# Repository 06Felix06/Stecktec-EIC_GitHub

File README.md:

# Stecktec EIC – Easy Irrigation Control

**Ein modulares, solarbetriebenes Bewässerungssystem mit eigenen Platinen, LoRa-Funk, Mobilfunk-Anbindung und Smartphone-App.**

Maturaprojekt (Abschlussprojekt) im Schuljahr 2024/25 an der Technologischen Fachoberschule Meran „Oskar von Miller“, Fachrichtung Elektrotechnik – von Felix Steck.

<p align="center">
  
  &nbsp;
  
</p>

<p align="center"><em>Hauptplatine (links) und Sensorplatine (rechts) – beide selbst in KiCad entworfen</em></p>

**Die komplette Projektdokumentation (64 Seiten) liegt hier: [docs/Projektdokumentation_StecktecEIC.pdf](docs/Projektdokumentation_StecktecEIC.pdf)**

---

## Inhalt

- [Was ist Stecktec EIC?](#was-ist-stecktec-eic)
- [Idee und Motivation](#idee-und-motivation)
- [Wie das System funktioniert](#wie-das-system-funktioniert)
- [Hardware](#hardware)
- [Software](#software)
- [Was nicht nach Plan lief](#was-nicht-nach-plan-lief)
- [Projekt in Zahlen](#projekt-in-zahlen)
- [Aufbau des Repositorys](#aufbau-des-repositorys)
- [Fazit](#fazit)
- [Lizenz](#lizenz)

---

## Was ist Stecktec EIC?

Stecktec EIC ist ein modulares intelligentes Bewässerungssystem, das speziell für den Einsatz im Obst- und Beerenanbau, aber auch für private Gärten konzipiert wurde. Es besteht aus mehreren modularen Teilen und kann verschiedene Werte wie die Bodenfeuchtigkeit, Temperatur und Luftfeuchtigkeit messen und Bewässerungsventile schalten. Alles wird über eine benutzerfreundliche Smartphone-App gesteuert und überwacht. Das ermöglicht dem Bauern eine optimale Übersicht und Kontrolle über seine Felder.

**EIC** steht für **Easy Irrigation Control** – eine einfache und effiziente Steuerung der Bewässerung, mit dem Ziel, den Wasserverbrauch zu verringern.

Kurz gesagt kann das System:

- **Bodenfeuchte messen** – mit einem Watermark-Saugspannungssensor (Irrometer 200SS), der misst, wie viel Wasser die Pflanze wirklich aus dem Boden ziehen kann
- **Temperatur und Luftfeuchtigkeit messen** (BME280)
- **Magnetventile schalten** – bistabile 12-V-Ventile, die nur beim Umschalten Strom brauchen
- **Kilometerweit funken** – Sensorstationen sprechen per LoRa mit der Hauptstation
- **Online gehen** – die Hauptstation ist per Mobilfunk (SIM7000) mit einer Firebase-Datenbank verbunden
- **Per App bedient werden** – eigene React-Native-App für Android und iOS
- **Autark laufen** – 18650-Akkus, die über ein kleines Solarpanel geladen werden

## Idee und Motivation

Die Idee zum EIC-Bewässerungssystem entstand aus der Beobachtung, dass viele bestehende landwirtschaftliche Bewässerungslösungen entweder zu teuer, zu kompliziert oder unzureichend automatisiert sind. Insbesondere kleinere landwirtschaftliche Betriebe oder Privatpersonen verfügen häufig nicht über die Mittel, um teure Systeme mit vielen unnötigen Funktionen zu implementieren. Ziel war es daher, ein kostengünstiges, modulares und leicht erweiterbares System zu entwickeln, das zuverlässig arbeitet und sich an verschiedene Bedürfnisse anpassen lässt.

Ein weiterer wichtiger Beweggrund war die zunehmende Regulierung des landwirtschaftlichen Wasserverbrauchs. Die Anforderungen an einen sparsamen und nachhaltigen Umgang mit Wasser steigen stetig. Bereits heute wird vielerorts auf ressourcenschonende Systeme wie Tröpfchenbewässerung umgestellt. Eine intelligente Steuerung kann diesen Trend weiter unterstützen, indem sie den Wasserverbrauch anhand aktueller Sensordaten zusätzlich optimiert und nur dann bewässert, wenn es tatsächlich notwendig ist.

Die Idee kam direkt vom eigenen Apfelbetrieb der Familie in Südtirol: Mein Vater hat oft davon gesprochen, wie praktisch ein intelligentes Bewässerungssystem wäre – und ich wollte ein Projekt umsetzen, das einen echten Nutzen im Alltag hat.

## Wie das System funktioniert

Das System besteht aus einer **Hauptstation** und einer oder mehreren **Sensorstationen**, die im Feld verteilt werden. Jede Station hat ihre eigene Basisplatine mit Mikrocontroller, Akku und Solarversorgung.

Die grafische Darstellung veranschaulicht, wie alle einzelnen Komponenten miteinander kommunizieren – sei es über LoRa, Internet oder über direkte Hardwareverbindungen.

Der Datenfluss im Überblick:

```mermaid
flowchart LR
    subgraph Feld
        S["Sensorstation<br/>ATmega328P · BME280 ·<br/>Watermark · 2 Ventile"]
        H["Hauptstation<br/>ATmega328P · 4 Ventile ·<br/>Durchflusssensoren"]
    end
    S <-- "LoRa (E32)" --> H
    H -- "Mobilfunk (SIM7000)<br/>HTTP" --> P["Proxy-Server<br/>(Node.js, AWS)"]
    P -- HTTPS --> F[("Firebase<br/>Realtime Database")]
    F <--> A["Smartphone-App<br/>(React Native)"]
```

1. Die **Hauptstation** schickt alle paar Sekunden ein JSON-Paket per LoRa an die Sensorstation – darin stehen u. a. die gewünschten Ventilzustände.
2. Die **Sensorstation** schaltet daraufhin ihre Ventile und antwortet mit ihren Messwerten (Temperatur, Luftfeuchtigkeit, Bodenfeuchte, Durchflussstatus).
3. Die Hauptstation lädt die Werte über das **SIM7000-Modul** in die **Firebase-Datenbank** hoch und liest dort die Ventilbefehle aus der App aus.
4. Da das SIM7000 kein HTTPS kann, Firebase aber nur HTTPS akzeptiert, sitzt dazwischen ein kleiner **Proxy-Server**, der die HTTP-Anfragen entgegennimmt und als HTTPS an Firebase weiterleitet.
5. In der **App** sieht man alle Wiesen, Sensorwerte als Diagramme und kann die Ventile manuell oder per Timer schalten.

## Hardware

Das gesamte System wurde bewusst modular aufgebaut, indem die Funktionen auf mehrere Unterplatinen verteilt wurden. Diese Aufteilung bietet entscheidende Vorteile in Bezug auf Wartung, Erweiterbarkeit und Fehlersuche. Durch die Trennung der Hauptfunktionen – wie Stromversorgung, Sensorik, Steuerung und Aktorik – auf eigene Platinen kann jede Komponente unabhängig getestet und bei Bedarf ausgetauscht oder erweitert werden, ohne das Gesamtsystem zu beeinträchtigen.

Alle Platinen wurden mit **KiCad** gezeichnet und bei **JLCPCB** gefertigt; bestückt habe ich sie selbst von Hand. Die Erweiterungsplatinen werden über beschriftete Pinheader mit Verdrehschutz auf die Basisplatinen gesteckt.

| Platine | Aufgabe | Ordner |
|---|---|---|
| **Hauptplatine V2** | Herzstück: ATmega328P, LoRa, SIM7000, 4 Ventile über Port-Expander + 2× L298, Analog-Multiplexer für Durchflusssensoren, 6 Lagen, 80 × 100 mm | [`hardware/01_Hauptplatine_V2`](hardware/01_Hauptplatine_V2) |
| **Sensorplatine** | ATmega328P, LoRa, BME280, Messschaltung für den Watermark-Sensor, 20-poliger Erweiterungsanschluss, 4 Lagen | [`hardware/02_Sensorplatine`](hardware/02_Sensorplatine) |
| **Magnetventilsteuerung** | Aufsteckmodul für die Sensorplatine: L298P-H-Brücke für 2 Ventile + 5→12-V-Step-Up (LM3478) | [`hardware/03_Magnetventilsteuerung`](hardware/03_Magnetventilsteuerung) |
| **Solarversorgung V2** | Laden der 18650-Akkus per Solarzelle oder 5-V-Netzteil (TP5400), 5 V + 3,3 V (DC-DC) | [`hardware/04_Solarversorgung_V2`](hardware/04_Solarversorgung_V2) |
| **Programmiergerät** | Brennt den Arduino-Bootloader und lädt danach Programme hoch – per USB-C, 2 Lagen | [`hardware/05_Programmiergeraet`](hardware/05_Programmiergeraet) |

Jeder Hardware-Ordner enthält das KiCad-Projekt (Schaltplan + Layout), wo vorhanden ein Schaltplan-PDF, eine interaktive Bestückungsliste (`ibom.html`, einfach im Browser öffnen) und unter `production/` die Gerber-Dateien, Stückliste und Bestückungsdaten.

### Hauptplatine

Die Hauptplatine bildet das Herzstück der EIC und vereint zahlreiche zuvor beschriebene Hardwarekomponenten auf einer kompakten Leiterplatte. Der zentrale Mikrocontroller ATmega328P-AU (Arduino-kompatibel) steuert alle angeschlossenen Module und übernimmt die gesamte Systemlogik.

Aufgrund der hohen Schaltungskomplexität und auch dank eines günstigen Angebots des Herstellers JLCPCB fiel die Entscheidung zugunsten einer sechs-Layer Platine. Dies ermöglichte die Platzierung separater Versorgungspolygone für +5 V, +3.3 V und GND auf den inneren Layern. Dadurch blieben sowohl der oberste (Top) als auch der unterste (Bottom) Layer sowie Layer 4 weitgehend frei von Versorgungsleitungen, was erheblich Platz für die Signalführung schuf und das Routen erleichterte.

Weitere Design-Entscheidungen: Testpunkte für die Inbetriebnahme, große Bauteile (SIM-Modul, Elkos, Akkuhalter) auf der Rückseite, alle Bauteile von Hand lötbar, und der 12-V-Step-Up für die Ventile wurde mit TI WEBENCH dimensioniert.

<p align="center"><em>Layout der Hauptplatine: V1 mit ESP32-S3 (links) und die finale V2 mit ATmega328P (rechts)</em></p>

### Sensorplatine

Für Erweiterungen verfügt die Sensorplatine über zwei Pinheader, auf die Zusatzmodule aufgesteckt werden können – zum Beispiel die Ventilsteuerungsplatine, mit der über eine H-Brücke (L298) zwei Magnetventile angesteuert werden können. Die Belegung der Pinheader wurde bewusst so gestaltet, dass auch beliebige andere Erweiterungen realisierbar sind.

Der **Watermark-Sensor** wird nicht dauerhaft, sondern nur kurz für die Messung bestromt – und die Polarität wird dabei umgedreht. Sonst würden Elektrolyseprozesse im Sensor die Messwerte verfälschen und seine Lebensdauer verkürzen.

### Programmiergerät

Um den Umgang mit dem ATmega Chip zu erleichtern, habe ich ein eigenes Programmiergerät entwickelt, das zwei zentrale Funktionen in einem kompakten Aufbau vereint: das Brennen des Bootloaders auf einen ATmega328P-Mikrocontroller und das anschließende Hochladen von Programmen. Außerdem kann durch die Code-Upload-Funktion der Platz und die Kosten für die USB-TTL-Converter-Schaltung auf der zu programmierenden Platine eingespart werden, was sich vor allem bei einer Serienproduktion lohnen würde.

Über vier Jumperleisten wechselt man zwischen **Bootloader-Modus** (das Gerät arbeitet wie ein Arduino Nano als ISP-Programmer über SPI) und **Code-Upload-Modus** (der USB-TTL-Wandler wird direkt mit dem Zielchip verbunden, der PC erkennt das Ganze wie einen normalen Arduino Nano).

Passende 3D-Druck-Gehäuse für Sensorstation und Programmiergerät liegen in [`hardware/3D-Gehaeuse`](hardware/3D-Gehaeuse).

## Software

| Teil | Technik | Ordner |
|---|---|---|
| Firmware Hauptplatine | C++ / PlatformIO, TinyGSM, EByte-LoRa-E32-Library, Adafruit MCP23X17, ArduinoJson | [`firmware/hauptplatine`](firmware/hauptplatine) |
| Firmware Sensorplatine | C++ / PlatformIO, EByte-LoRa-E32-Library, BME280_Light | [`firmware/sensorplatine`](firmware/sensorplatine) |
| Testprogramme | Einzeltests für jede Baugruppe (LoRa, SIM7000, H-Brücke, Watermark, I²C …) | [`firmware/tests`](firmware/tests) |
| Proxy-Server | Node.js / Express, HTTP → HTTPS zu Firebase | [`server/proxy`](server/proxy) |
| Smartphone-App | React Native (Expo), Firebase Auth + Realtime Database | [`app`](app) |

### LoRa-Kommunikation

Die Kommunikation zwischen der Hauptplatine und der Sensorplatine erfolgt über das LoRa E32-Modul und ist bidirektional durch die sogenannte Master-Slave-Kommunikation. Das bedeutet, die Hauptplatine sendet ein Datenpaket, auf das das Sensor-Modul mit einer Antwort reagiert. Die Sensorplatine sendet ein Datenpaket nur dann, wenn sie zuvor ein Datenpaket von der Hauptplatine empfangen hat. Dieses Kommunikationssystem hilft, den Stromverbrauch der Sensorplatine erheblich zu minimieren.

### Ventilansteuerung

Weil einfache H-Brücken-ICs verwendet werden, darf es beim Umschalten nie einen Moment geben, in dem beide Steuerpins gleichzeitig einen Kurzschluss verursachen. Deshalb wird zuerst der Enable-Pin deaktiviert, dann umgeschaltet, und erst danach wieder freigegeben (siehe [`firmware/hauptplatine/src/MainFunctions.h`](firmware/hauptplatine/src/MainFunctions.h)).

### Mobilfunk und Datenbank

Die Hauptplatine baut die Mobilfunkverbindung (Hologram-IoT-SIM) nur kurz für jede Anfrage auf und trennt sie danach wieder, um Strom zu sparen. Zwei Funktionen reichen für die gesamte Kommunikation: `putValue(path, value)` schreibt einen Wert in die Datenbank, `getValue(path)` liest einen aus.

Die Entwicklung dieses Teils war eine der komplexesten Phasen im Projekt und erstreckte sich über mehrere Monate, was auch den Zeitplan etwas durcheinanderbrachte. Erst nach umfassender Recherche und Debugging konnte eine stabile Anbindung an die Firebase-Datenbank realisiert werden.

### Smartphone-App

Im Tab „Wiesen Config“ können neue Wiesen angelegt und bestehende verwaltet werden. Jeder Eintrag enthält eine eindeutige ID, einen frei wählbaren Namen und die Seriennummer der dazugehörigen Hauptplatine. Zu jeder Wiese (Hauptmodul) können bis zu fünf Sensormodule hinzugefügt werden. Durch ein Rufzeichen-Symbol ist sofort erkennbar, bei welcher Wiese ein Problem vorliegt.

Im Bereich **Manuell** lassen sich die Ventile direkt oder per Timer schalten (praktisch z. B., um ein Leck im Tropfschlauch zu finden), unter **Sensoren** werden die Messwerte als Diagramme angezeigt. Der **Automatik**-Modus (Bewässerung nach Zeitplan oder Bodenfeuchte) war zum Projektende noch in Entwicklung.

## Was nicht nach Plan lief

Ein großer Teil des Projekts war Fehlersuche – und genau daraus habe ich am meisten gelernt:

- **ESP32-S3 → ATmega328P:** Die erste Hauptplatine basierte auf einem ESP32-S3. Das Hochladen war extrem unzuverlässig, und trotz deaktiviertem WLAN und Bluetooth lag der Ruhestrom bei über 100 mA – viel zu viel für ein Solar-System. Also habe ich zügig eine V2 mit dem ATmega328P entworfen, der auf der Sensorplatine schon funktionierte.
- **SIM7080G → SIM7000:** Das ursprünglich geplante SIM7080G-Modul ließ sich nicht in Betrieb nehmen; erst mit dem SIM7000 klappte die Verbindung. Auch der Versuch, das Modul direkt über AT-Befehle zu steuern, scheiterte an unzuverlässigen Antworten – die TinyGSM-Library war die Lösung.
- **Solarversorgung V1:** Der Laderegler (CN3791) und der Schutz-IC (DW01A) funktionierten auf der ersten Version nicht, vermutlich wegen Layoutfehlern. Für die V2 habe ich auf den TP5400 gewechselt und den Layoutvorschlag aus dem Datenblatt fast 1:1 übernommen – danach lief sie auf Anhieb.
- **Der falsche Chip:** Es gibt zwei nahezu baugleiche Modelle – den MCP23017 und den MCP23S17. Der entscheidende Unterschied besteht darin, dass der MCP23017 über I2C und der MCP23S17 über SPI angesteuert wird. Dies habe ich bei der Bestellung jedoch übersehen und versehentlich den MCP23S17 bestellt und aufgelötet. Nachdem ich den korrekten MCP23017 eingebaut hatte, funktionierte der Port Expander auf Anhieb problemlos.
- **Offene Punkte:** Der gleichzeitige Betrieb von Port-Expander und SIM-Modul führte noch zu Fehlfunktionen (vermutlich Timer- bzw. Library-Konflikte), und der ATmega328P stößt mit allen Modulen gleichzeitig an seine Grenzen.

Die ersten Versionen von Hauptplatine und Solarversorgung liegen zum Vergleich in [`hardware/archiv_V1`](hardware/archiv_V1).

## Projekt in Zahlen

| | |
|---|---|
| Zeitraum | Schuljahr 2024/25, 35 Wochen |
| Arbeitsstunden | **307 h** (Schule, zu Hause und offenes Labor) |
| Eigene Platinen-Designs | 7 (davon 5 in der finalen Version) |
| Materialkosten Prototyp | **ca. 424 €** (Platinen 57 €, Bauteile 168 €, Module 199 €) |
| Geschätzte Kosten in Serie (100 Stk.) | ca. 307 € pro komplettem System |
| Akkulaufzeit ohne Nachladen | ca. eine Woche |

Projektantrag, Pflichtenheft und weitere Planungsunterlagen liegen in [`docs/projektmanagement`](docs/projektmanagement).

## Aufbau des Repositorys

```
├── app/                     React-Native-App (Expo)
├── docs/
│   ├── Projektdokumentation_StecktecEIC.pdf
│   ├── Auslageblatt.pdf
│   ├── images/              Bilder für dieses README
│   └── projektmanagement/   Projektantrag, Pflichtenheft, Blockschaltbild
├── firmware/
│   ├── hauptplatine/        Finaler Code Hauptplatine (PlatformIO)
│   ├── sensorplatine/       Finaler Code Sensorplatine (PlatformIO)
│   └── tests/               Testprogramme für die einzelnen Baugruppen
├── hardware/
│   ├── 01_Hauptplatine_V2/
│   ├── 02_Sensorplatine/
│   ├── 03_Magnetventilsteuerung/
│   ├── 04_Solarversorgung_V2/
│   ├── 05_Programmiergeraet/
│   ├── 3D-Gehaeuse/         STL-Dateien für den 3D-Druck
│   └── archiv_V1/           Erste Versionen (Hauptplatine mit ESP32, Solarversorgung V1)
└── server/proxy/            Node.js-Proxy zwischen SIM-Modul und Firebase
```

**Hinweis zum Nachbauen:** Zugangsdaten (Firebase-Konfiguration, Proxy-IP, Service-Account-Schlüssel) wurden aus dem öffentlichen Code entfernt und durch Platzhalter wie `YOUR_PROXY_IP` bzw. `YOUR_API_KEY` ersetzt. Wer das System selbst aufsetzen möchte, braucht ein eigenes Firebase-Projekt und einen eigenen Server für den Proxy.

## Fazit

Mit dem EIC-Bewässerungssystem wurde ein praxisnahes und zukunftsorientiertes Projekt umgesetzt, das moderne Technik mit den realen Anforderungen der Landwirtschaft verbindet.

Natürlich lief nicht alles exakt nach Plan – einige Funktionen konnten innerhalb des Projektzeitraums nicht vollständig umgesetzt werden. Dennoch habe ich gerade aus diesen Herausforderungen wertvolle Erfahrungen gewonnen, die mir bei zukünftigen Projekten helfen werden, realistischer zu planen und flexibler auf unerwartete Schwierigkeiten zu reagieren.

Das Projekt hat meine Begeisterung für die Entwicklung intelligenter, nachhaltiger Lösungen gestärkt und mir gezeigt, wie viel Potenzial in der Verbindung von Technik und Umwelt steckt.

## Lizenz

Dieses Projekt steht unter der Lizenz [Creative Commons Namensnennung – Nicht kommerziell 4.0 International (CC BY-NC 4.0)](https://creativecommons.org/licenses/by-nc/4.0/deed.de). Siehe [LICENSE](LICENSE).

Betreut von Martin De Tomaso und Ivan Huber, TFO Meran.

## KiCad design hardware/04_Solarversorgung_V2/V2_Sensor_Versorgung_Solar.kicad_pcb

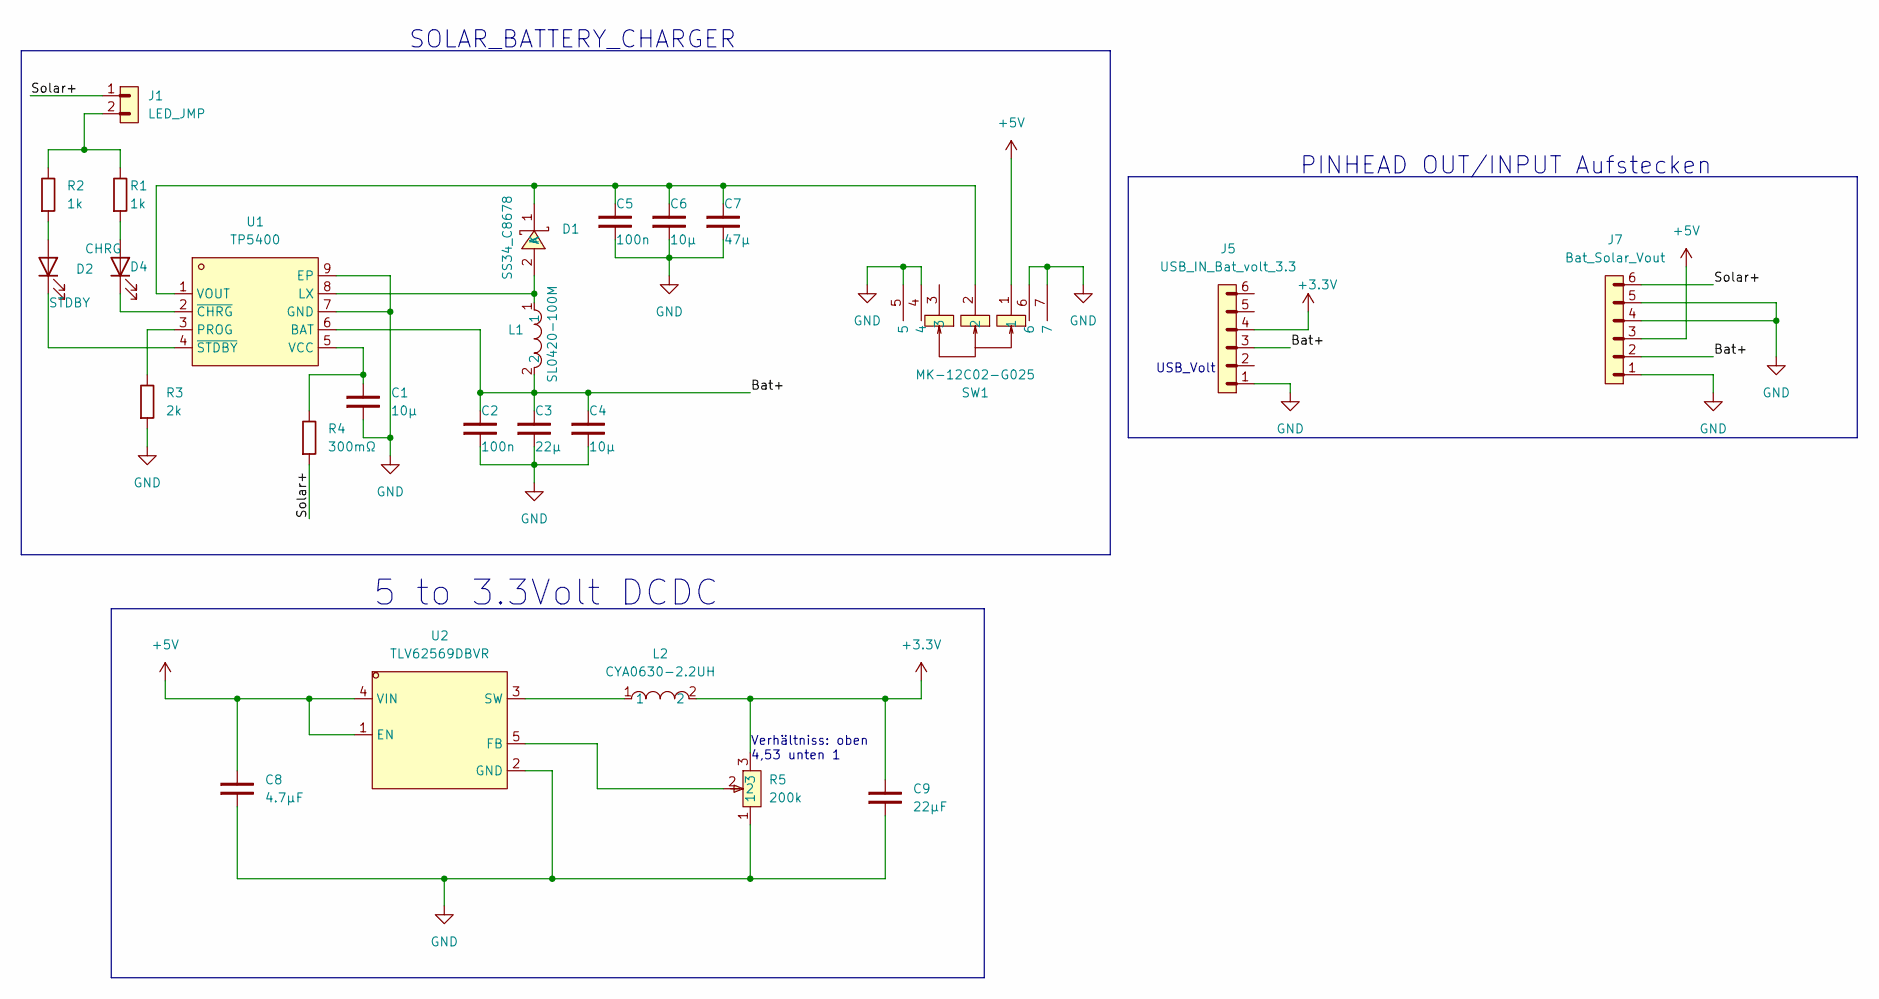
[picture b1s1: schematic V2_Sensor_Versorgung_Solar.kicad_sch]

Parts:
C1, C4, C6: 10µ; C_0805_2012Metric
C2, C5: 100n; C_0805_2012Metric
C3: 22µ; C_0805_2012Metric
C7: 47µ; C_0805_2012Metric
C8: 4.7µF; C_0805_2012Metric
C9: 22µF; C_0805_2012Metric
D1: SS34_C8678; SMA_L4.3-W2.6-LS5.2-RD; LCSC Part C8678
D2: STDBY; LED_0805_2012Metric
D4: CHRG; LED_0805_2012Metric
J1: LED_JMP; PinHeader_1x02_P2.54mm_Vertical
J5: USB_IN_Bat_volt_3.3; PinHeader_1x06_P2.54mm_Vertical
J7: Bat_Solar_Vout; PinHeader_1x06_P2.54mm_Vertical
L1: SL0420-100M; IND-SMD_L4.5-W4.1_SL0420; LCSC Part C22463809
L2: CYA0630-2.2UH; IND-SMD_L7.2-W6.6_GPSR07X0; LCSC Part C5189746
R1, R2: 1k; R_0805_2012Metric
R3: 2k; R_0805_2012Metric
R4: 300mΩ; R_0805_2012Metric
R5: 200k; RES-ADJ-SMD_VG039NCH; LCSC Part C128558
SW1: MK-12C02-G025; SW-SMD_MK-12C02-G025; LCSC Part C778186
U1: TP5400; ESOP-8_L4.9-W3.9-P1.27-LS6.0-BL-EP; LCSC Part C2891434
U2: TLV62569DBVR; SOT-23-5_L3.0-W1.7-P0.95-LS2.8-BR; LCSC Part C141836

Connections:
+3.3V: C9.2, J5.4, L2.2, R5.3
+5V: C8.2, J7.3, SW1.1, U2.1 (EN), U2.4 (VIN)
/Bat+: C2.2, C3.2, C4.2, J5.3, J7.2, L1.2, U1.6 (BAT)
/Solar+: J1.1, J7.6, R4.1
GND: C1.1, C2.1, C3.1, C4.1, C5.1, C6.1, C7.1, C8.1, C9.1, J5.1, J7.1, J7.4, J7.5, R3.1, R5.1, SW1.4, SW1.5, SW1.6, SW1.7, U1.7 (GND), U1.9 (EP), U2.2 (GND)
unnamed: D1.2 (A), L1.1, U1.8 (LX)
unnamed: C5.2, C6.2, C7.2, D1.1 (K), SW1.2, U1.1 (VOUT)
unnamed: D2.2 (A), R2.1
unnamed: D2.1 (K), U1.4 (~STDBY)
unnamed: D4.2 (A), R1.1
unnamed: D4.1 (K), U1.2 (~CHRG)
unnamed: J1.2, R1.2, R2.2
unnamed: R3.2, U1.3 (PROG)
unnamed: C1.2, R4.2, U1.5 (VCC)
unnamed: R5.2, U2.5 (FB)
unnamed: L2.1, U2.3 (SW)

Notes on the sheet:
PINHEAD OUT/INPUT Aufstecken
SOLAR_BATTERY_CHARGER
5 to 3.3Volt DCDC
USB_Volt
Verhältniss: oben 4,53 unten 1

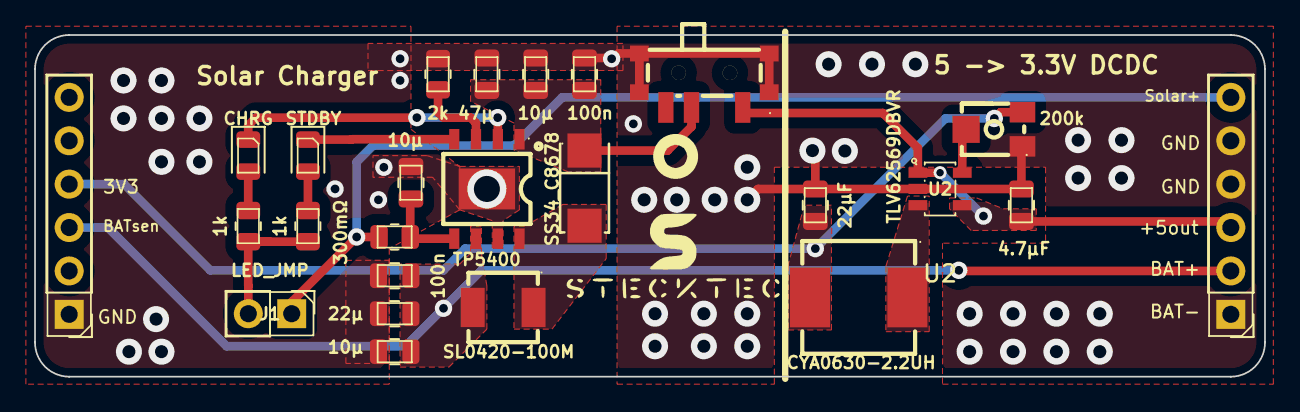
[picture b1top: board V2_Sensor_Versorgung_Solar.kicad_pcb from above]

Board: 2 copper layers, 72.0 x 20.0 mm, 25 parts (0 on the bottom side), 16 nets.

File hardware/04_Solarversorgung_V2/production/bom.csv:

Designator,Footprint,Quantity,Value,LCSC Part #
"C1, C4, C6",0805,3,10µ,
"C2, C5",0805,2,100n,
C3,0805,1,22µ,
C7,0805,1,47µ,
C8,0805,1,4.7µF,
C9,0805,1,22µF,
D1,SMA_L4.3-W2.6-LS5.2-RD,1,SS34_C8678,C8678
D2,0805,1,STDBY,
D4,0805,1,CHRG,
J1,PinHeader_1x02_P2.54mm_Vertical,1,LED_JMP,
J5,PinHeader_1x06_P2.54mm_Vertical,1,USB_IN_Bat_volt_3.3,
J7,PinHeader_1x06_P2.54mm_Vertical,1,Bat_Solar_Vout,
L1,IND-SMD_L4.5-W4.1_SL0420,1,SL0420-100M,C22463809
L2,IND-SMD_L7.2-W6.6_GPSR07X0,1,CYA0630-2.2UH,C5189746
"R1, R2",0805,2,1k,
R3,0805,1,2k,
R4,0805,1,300mΩ,
R5,RES-ADJ-SMD_VG039NCH,1,200k,C128558
SW1,SW-SMD_MK-12C02-G025,1,MK-12C02-G025,C778186
U1,ESOP-8_L4.9-W3.9-P1.27-LS6.0-BL-EP,1,TP5400,C2891434
U2,SOT-23-5_L3.0-W1.7-P0.95-LS2.8-BR,1,TLV62569DBVR,C141836

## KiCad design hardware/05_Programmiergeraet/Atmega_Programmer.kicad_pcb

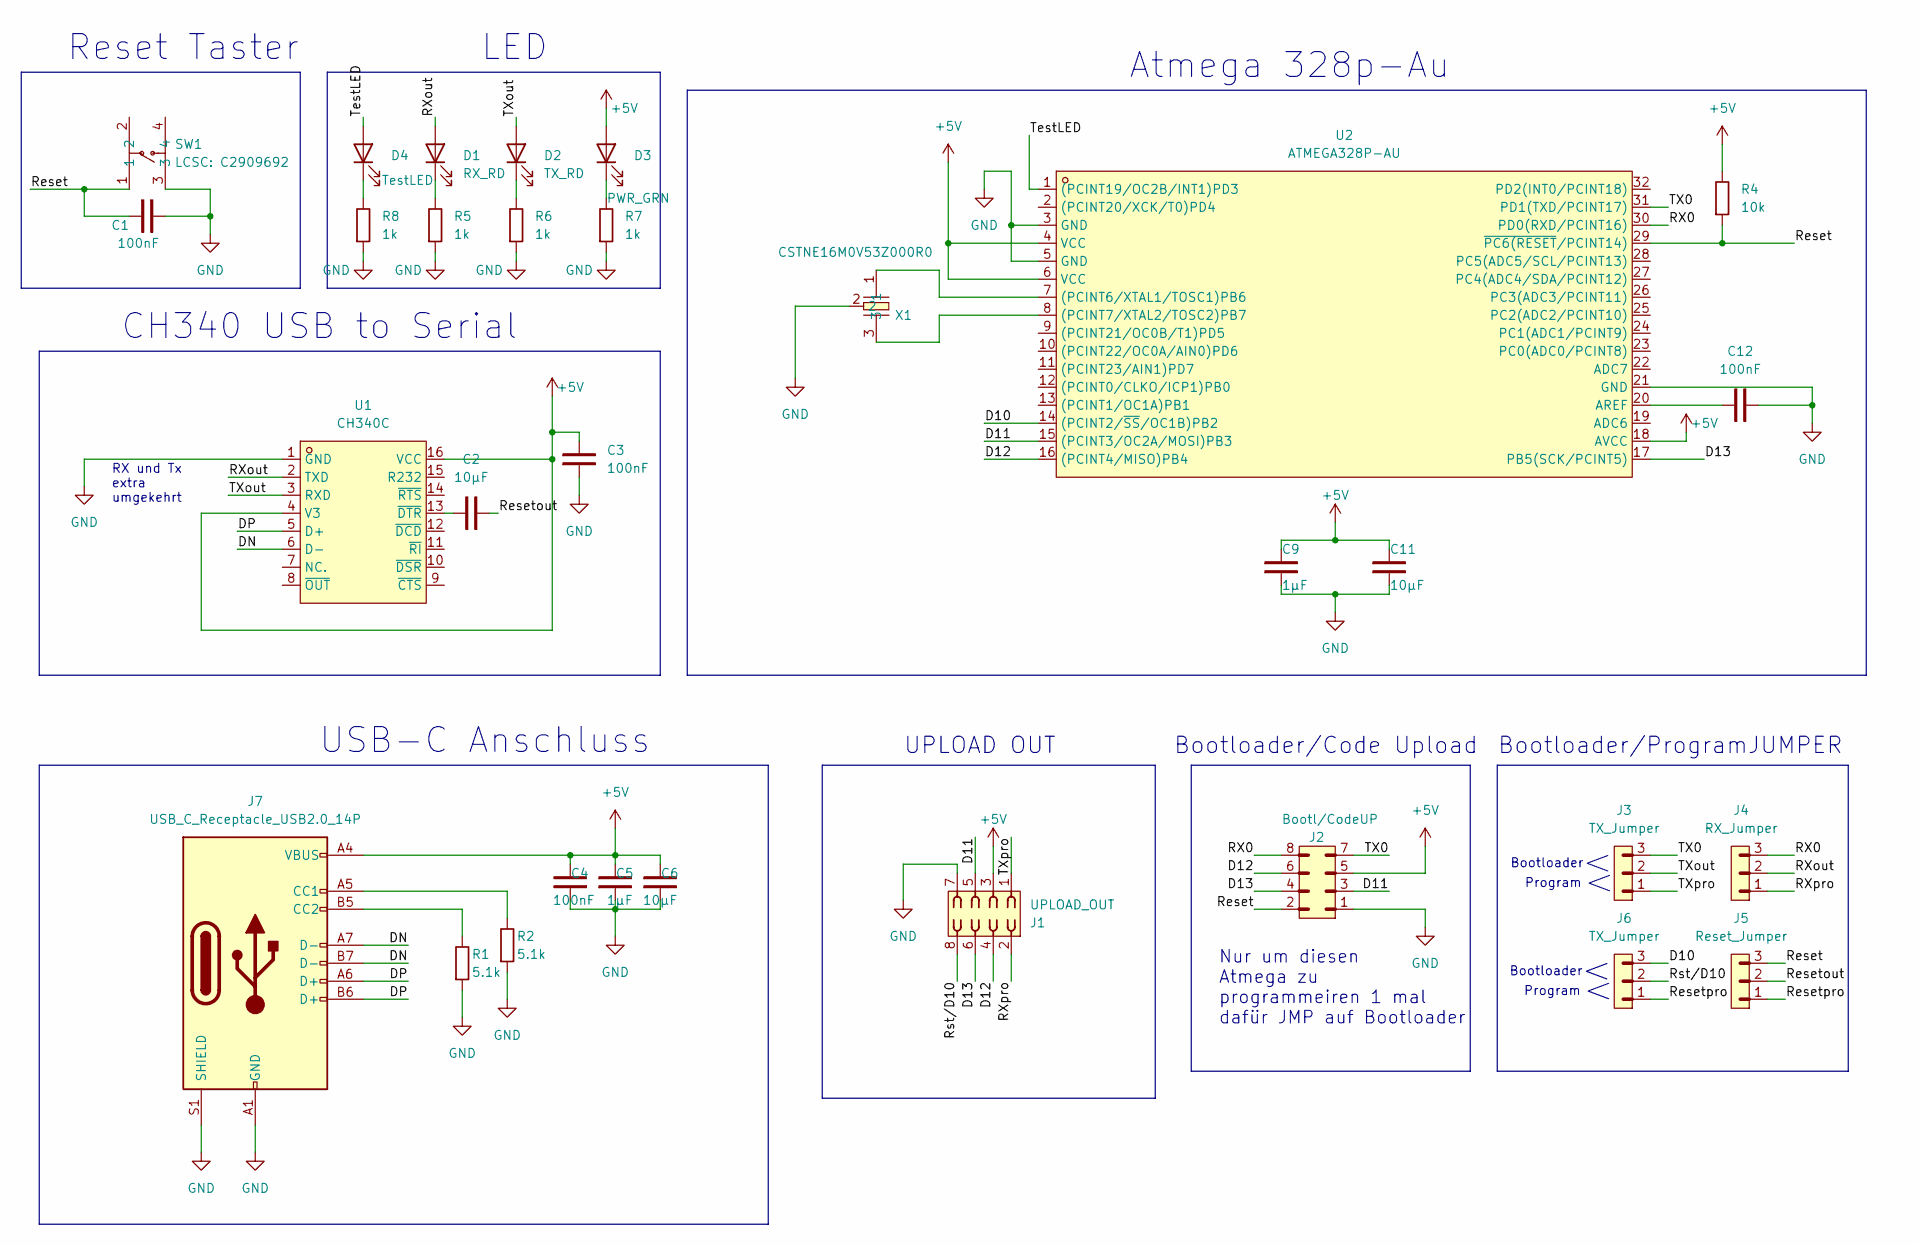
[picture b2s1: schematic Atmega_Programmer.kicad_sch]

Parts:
C1, C3, C4, C12: 100nF; C_0805_2012Metric
C2, C6, C11: 10µF; C_0805_2012Metric
C5, C9: 1µF; C_0805_2012Metric
D1: RX_RD; LED_0805_2012Metric
D2: TX_RD; LED_0805_2012Metric
D3: PWR_GRN; LED_0805_2012Metric
D4: TestLED; LED_0805_2012Metric
J1: UPLOAD_OUT; PinSocket_2x04_P2.54mm_Vertical
J2: Bootl/CodeUP; PinHeader_2x04_P2.54mm_Vertical
J3, J6: TX_Jumper; PinHeader_1x03_P2.54mm_Vertical
J4: RX_Jumper; PinHeader_1x03_P2.54mm_Vertical
J5: Reset_Jumper; PinHeader_1x03_P2.54mm_Vertical
J7: USB_C_Receptacle_USB2.0_14P; USB_C_Receptacle_HRO_TYPE-C-31-M-12
R1, R2: 5.1k; R_0805_2012Metric
R4: 10k; R_0805_2012Metric
R5, R6, R7, R8: 1k; R_0805_2012Metric
SW1: LCSC: C2909692; SW-SMD_4P-L6.2-W6.2-P4.50-LS8.6; LCSC Part C2909692
U1: CH340C; SOP-16_L10.0-W3.9-P1.27-LS6.0-BL; LCSC Part C84681
U2: ATMEGA328P-AU; TQFP-32_L7.0-W7.0-P0.80-LS9.0-BL; LCSC Part C14877
X1: CSTNE16M0V53Z000R0; OSC-SMD_3P-L3.2-W1.3-P1.20-L; LCSC Part C783275

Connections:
+5V: C3.2, C4.1, C5.2, C6.2, C9.2, C11.2, D3.2 (A), J1.3, J2.5, J7.A4 (VBUS), J7.A9 (VBUS), J7.B4 (VBUS), J7.B9 (VBUS), R4.2, U1.4 (V3), U1.16 (VCC), U2.4 (VCC), U2.6 (VCC), U2.18 (AVCC)
/D10: J6.3, U2.14 ((PCINT2/~SS/OC1B)PB2)
/D11: J1.5, J2.3, U2.15 ((PCINT3/OC2A/MOSI)PB3)
/D12: J1.4, J2.6, U2.16 ((PCINT4/MISO)PB4)
/D13: J1.6, J2.4, U2.17 (PB5(SCK/PCINT5))
/DN: J7.A7 (D-), J7.B7 (D-), U1.6 (D-)
/DP: J7.A6 (D+), J7.B6 (D+), U1.5 (D+)
/RX0: J2.8, J4.3, U2.30 (PD0(RXD/PCINT16))
/RXout: D1.2 (A), J4.2, U1.2 (TXD)
/RXpro: J1.2, J4.1
/Reset: C1.1, J2.2, J5.3, R4.1, SW1.1, U2.29 (~PC6(RESET/PCINT14))
/Resetout: C2.1, J5.2
/Resetpro: J5.1, J6.1
/Rst/D10: J1.8, J6.2
/TX0: J2.7, J3.3, U2.31 (PD1(TXD/PCINT17))
/TXout: D2.2 (A), J3.2, U1.3 (RXD)
/TXpro: J1.1, J3.1
/TestLED: D4.2 (A), U2.1 ((PCINT19/OC2B/INT1)PD3)
GND: C1.2, C3.1, C4.2, C5.1, C6.1, C9.1, C11.1, C12.1, J1.7, J2.1, J7.A1 (GND), J7.A12 (GND), J7.B1 (GND), J7.B12 (GND), J7.S1 (SHIELD), R1.1, R2.1, R5.1, R6.1, R7.1, R8.1, SW1.3, U1.1 (GND), U2.3 (GND), U2.5 (GND), U2.21 (GND), X1.2
unnamed: D1.1 (K), R5.2
unnamed: D2.1 (K), R6.2
unnamed: D3.1 (K), R7.2
unnamed: D4.1 (K), R8.2
unnamed: J7.A5 (CC1), R2.2
unnamed: J7.B5 (CC2), R1.2
unnamed: C2.2, U1.13 (~DTR)
unnamed: U2.7 ((PCINT6/XTAL1/TOSC1)PB6), X1.1
unnamed: U2.8 ((PCINT7/XTAL2/TOSC2)PB7), X1.3
unnamed: C12.2, U2.20 (AREF)

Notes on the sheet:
Reset Taster
CH340 USB to Serial
Atmega 328p-Au
RX und Tx extra umgekehrt
USB-C Anschluss
Nur um diesen Atmega zu programmeiren 1 mal dafür JMP auf Bootloader
UPLOAD OUT
Bootloader
Bootloader/ProgramJUMPER
Bootloader/Code Upload
LED
Program

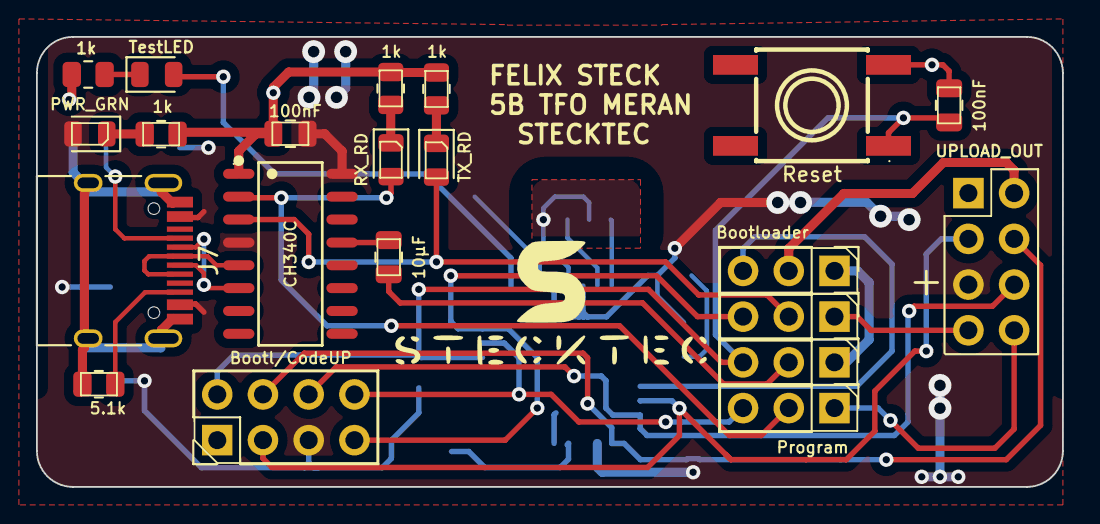
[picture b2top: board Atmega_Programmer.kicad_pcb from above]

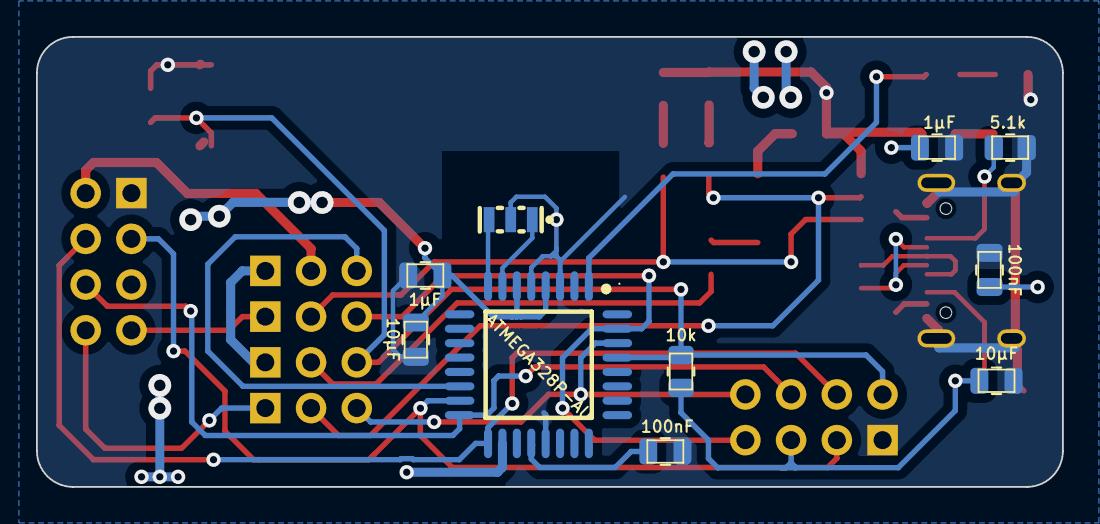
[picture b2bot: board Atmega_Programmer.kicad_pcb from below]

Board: 2 copper layers, 57.0 x 25.0 mm, 31 parts (10 on the bottom side), 29 nets.

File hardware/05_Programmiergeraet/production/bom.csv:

Designator,Footprint,Quantity,Value,LCSC Part #
"C1, C12, C2, C3, C4",0805,5,100nF,
"C11, C6",0805,2,10µF,
"C5, C9",0805,2,1µF,
D1,0805,1,RX_RD,
D2,0805,1,TX_RD,
D3,0805,1,PWR_GRN,
D4,0805,1,TestLED,
J1,PinSocket_2x04_P2.54mm_Vertical,1,UPLOAD_OUT,
J2,PinHeader_2x04_P2.54mm_Vertical,1,Bootl/CodeUP,
"J3, J6",PinHeader_1x03_P2.54mm_Vertical,2,TX_Jumper,
J4,PinHeader_1x03_P2.54mm_Vertical,1,RX_Jumper,
J5,PinHeader_1x03_P2.54mm_Vertical,1,Reset_Jumper,
J7,USB_C_Receptacle_HRO_TYPE-C-31-M-12,1,USB_C_Receptacle_USB2.0_14P,
"R1, R2",0805,2,5.1k,
R4,0805,1,10k,
"R5, R6, R7, R8",0805,4,1k,
SW1,SW-SMD_4P-L6.2-W6.2-P4.50-LS8.6,1,Reset,C2909692
U1,SOP-16_L10.0-W3.9-P1.27-LS6.0-BL,1,CH340C,C84681
U2,TQFP-32_L7.0-W7.0-P0.80-LS9.0-BL,1,ATMEGA328P-AU,C14877
X1,OSC-SMD_3P-L3.2-W1.3-P1.20-L,1,CSTNE16M0V53Z000R0,C783275

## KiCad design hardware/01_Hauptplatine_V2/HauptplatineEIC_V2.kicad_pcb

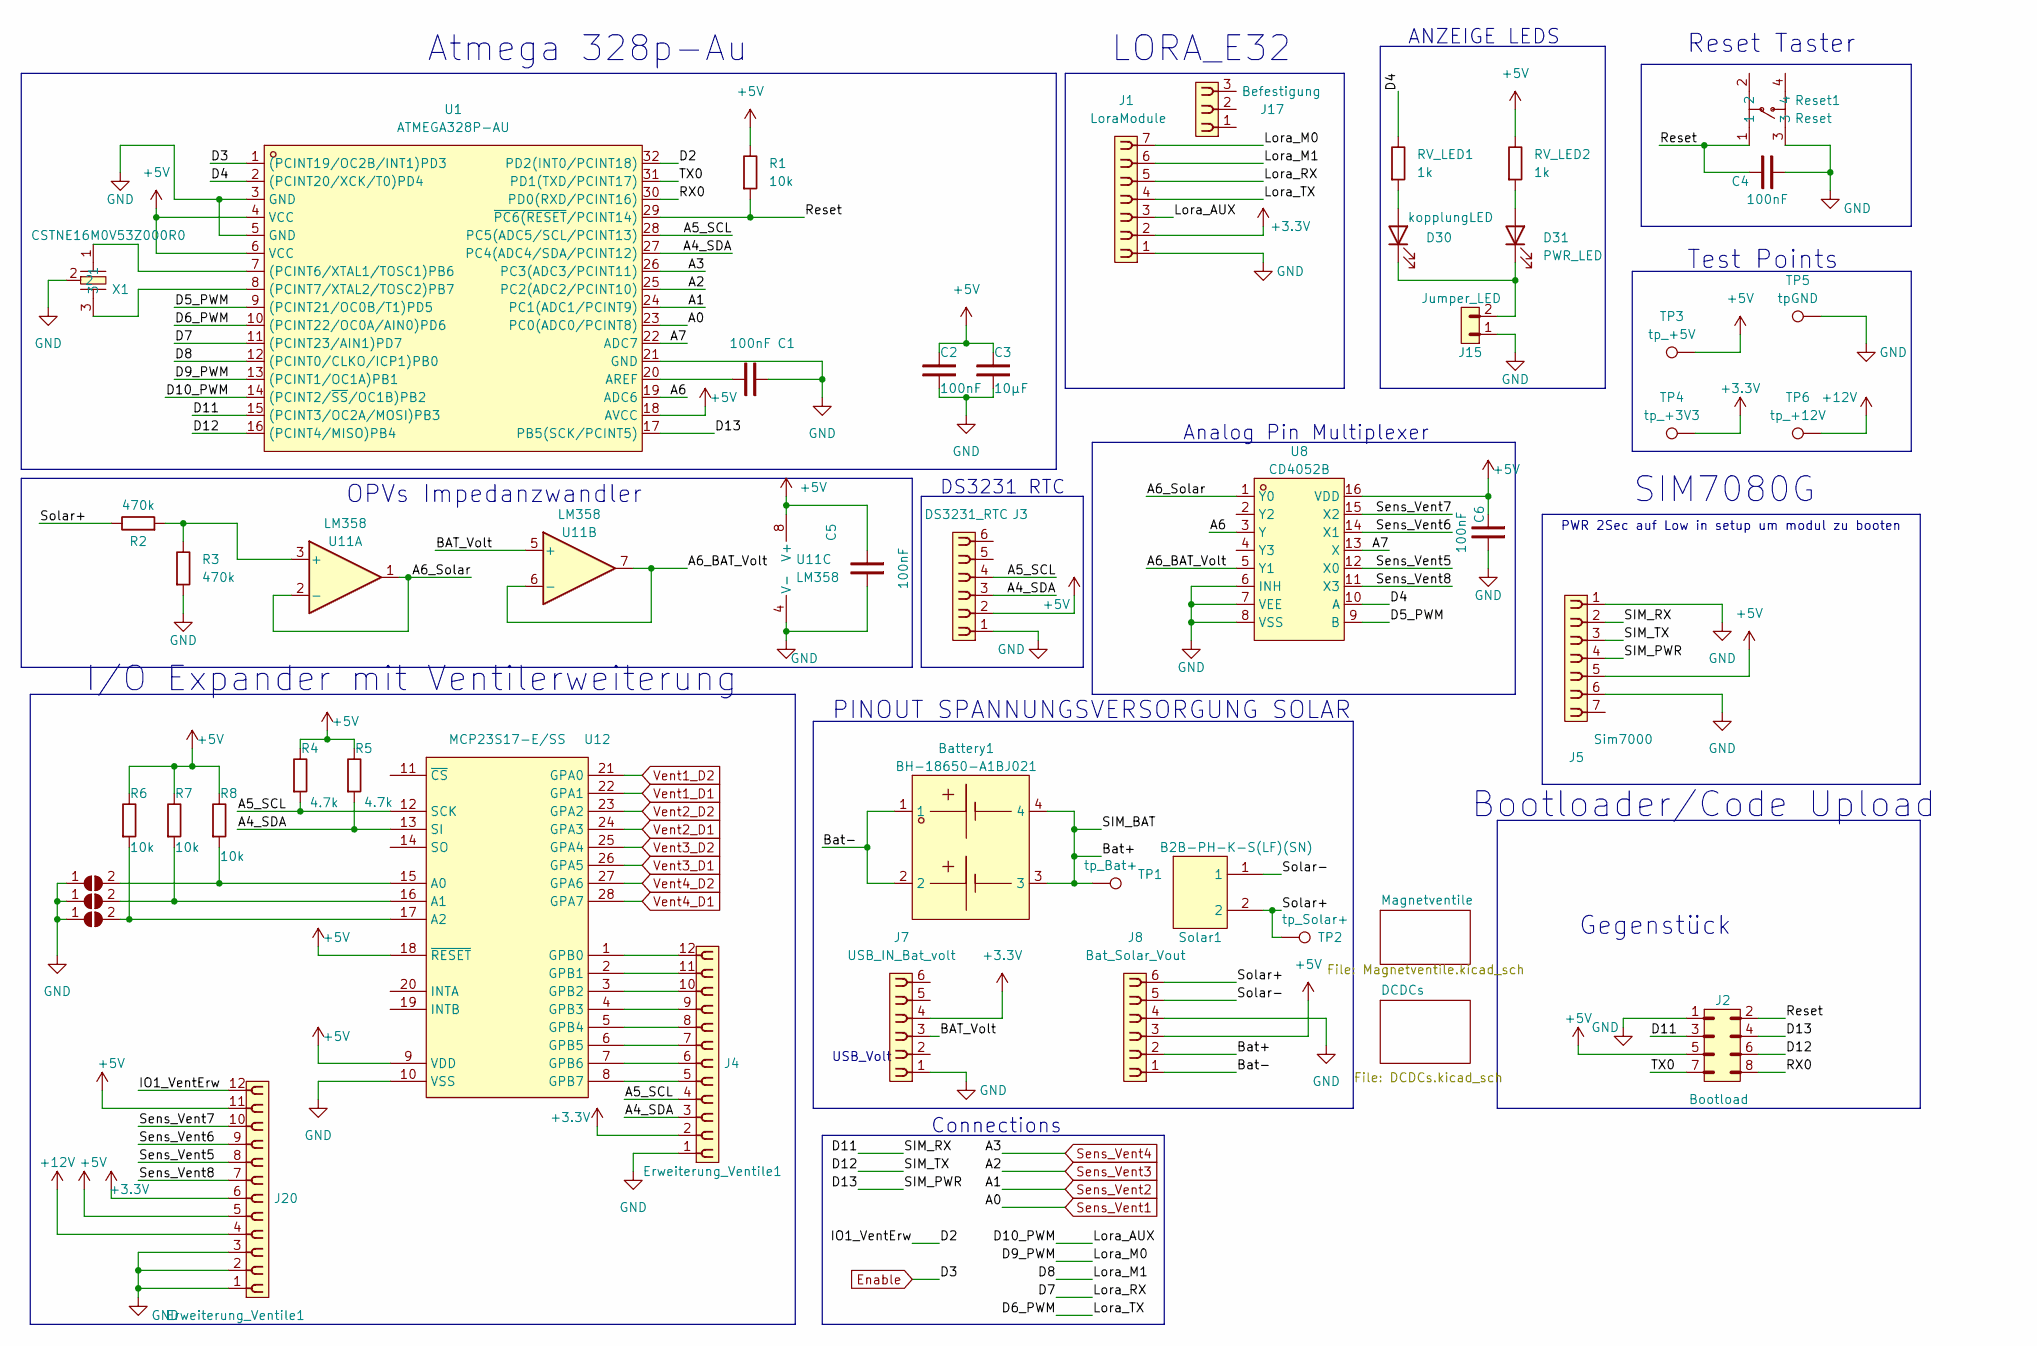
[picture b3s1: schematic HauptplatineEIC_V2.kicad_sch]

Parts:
Battery1: BH-18650-A1BJ021; BAT-TH_L77.0-W39.9_BH-18650-A1BJ021; LCSC Part C20606804
C1, C2, C4, C5, C6: 100nF; C_0805_2012Metric
C3: 10µF; C_0805_2012Metric
D30: kopplungLED; LED_0805_2012Metric
D31: PWR_LED; LED_0805_2012Metric
J1: LoraModule; PinSocket_1x07_P2.54mm_Vertical
J2: Bootload; PinHeader_2x04_P2.54mm_Vertical
J3: DS3231_RTC; PinSocket_1x06_P2.54mm_Vertical
J4, J20: Erweiterung_Ventile1; PinSocket_1x12_P2.54mm_Vertical
J5: Sim7000; PinSocket_1x07_P2.54mm_Vertical
J7: USB_IN_Bat_volt; PinSocket_1x06_P2.54mm_Vertical
J8: Bat_Solar_Vout; PinSocket_1x06_P2.54mm_Vertical
J15: Jumper_LED; PinHeader_1x02_P2.54mm_Vertical
J17: Befestigung; PinSocket_1x03_P2.54mm_Vertical
JP4, JP5, JP6: SolderJumper_2_Open; SolderJumper-2_P1.3mm_Open_Pad1.0x1.5mm
R1, R6, R7, R8: 10k; R_0805_2012Metric
R2, R3: 470k; R_0805_2012Metric
R4, R5: 4.7k; R_0805_2012Metric
RV_LED1, RV_LED2: 1k; R_0805_2012Metric
Reset1: Reset; SW-SMD_4P-L6.2-W6.2-P4.50-LS8.6; LCSC Part C2909692
Solar1: B2B-PH-K-S(LF)(SN); CONN-TH_B2B-PH-K-S; LCSC Part C131337
TP1: tp_Bat+; TPSteckFelix
TP2: tp_Solar+; TPSteckFelix
TP3: tp_+5V; TPSteckFelix
TP4: tp_+3V3; TPSteckFelix
TP5: tpGND; TPSteckFelix
TP6: tp_+12V; TPSteckFelix
U1: ATMEGA328P-AU; TQFP-32_L7.0-W7.0-P0.80-LS9.0-BL; LCSC Part C14877
U8: CD4052B; SOIC-16_L9.9-W3.9-P1.27-LS6.0-BL; LCSC Part C5356105
U11: LM358; SOIC-8_L5.0-W4.0-P1.27-LS6.0-BL
U12: MCP23S17-E/SS; SSOP-28_L10.2-W5.3-P0.65-LS7.8-BL; LCSC Part C148009
X1: CSTNE16M0V53Z000R0; OSC-SMD_3P-L3.2-W1.3-P1.20-L; LCSC Part C783275

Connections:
+3.3V: J1.2, J4.2, J7.4, J20.6, TP4.1
+5V: C2.2, C3.2, C5.1, C6.1, J2.5, J3.2, J5.5, J8.3, J20.5, J20.11, R1.2, R4.2, R5.2, R6.2, R7.2, R8.2, RV_LED2.2, TP3.1, U1.4 (VCC), U1.6 (VCC), U1.18 (AVCC), U8.16 (VDD), U11.8 (V+), U12.9 (VDD), U12.18 (~RESET); also elsewhere on the board
+12V: J20.4, TP6.1; also elsewhere on the board
/A4_SDA: J3.3, J4.3, R5.1, U1.27 (PC4(ADC4/SDA/PCINT12)), U12.13 (SI)
/A5_SCL: J3.4, J4.4, R4.1, U1.28 (PC5(ADC5/SCL/PCINT13)), U12.12 (SCK)
/A6: U1.19 (ADC6), U8.3 (Y)
/A6_BAT_Volt: U8.5 (Y1), U11.6 (-), U11.7
/A6_Solar: U8.1 (Y0), U11.1, U11.2 (-)
/A7: U1.22 (ADC7), U8.13 (X)
/BAT_Volt: J7.3, U11.5 (+)
/Bat+: Battery1.3, Battery1.4, J8.2, TP1.1
/Bat-: Battery1.1, Battery1.2, J8.1
/D2: J20.12, U1.32 (PD2(INT0/PCINT18))
/D4: RV_LED1.2, U1.2 ((PCINT20/XCK/T0)PD4), U8.10 (A)
/D5_PWM: U1.9 ((PCINT21/OC0B/T1)PD5), U8.9 (B)
/D6_PWM: J1.4, U1.10 ((PCINT22/OC0A/AIN0)PD6)
/D7: J1.5, U1.11 ((PCINT23/AIN1)PD7)
/D8: J1.6, U1.12 ((PCINT0/CLKO/ICP1)PB0)
/D9_PWM: J1.7, U1.13 ((PCINT1/OC1A)PB1)
/D10_PWM: J1.3, U1.14 ((PCINT2/~SS/OC1B)PB2)
/D11: J2.3, J5.2, U1.15 ((PCINT3/OC2A/MOSI)PB3)
/D12: J2.6, J5.3, U1.16 ((PCINT4/MISO)PB4)
/D13: J2.4, J5.4, U1.17 (PB5(SCK/PCINT5))
/RX0: J2.8, U1.30 (PD0(RXD/PCINT16))
/Reset: C4.1, J2.2, R1.1, Reset1.1, U1.29 (~PC6(RESET/PCINT14))
/Sens_Vent5: J20.8, U8.12 (X0)
/Sens_Vent6: J20.9, U8.14 (X1)
/Sens_Vent7: J20.10, U8.15 (X2)
/Sens_Vent8: J20.7, U8.11 (X3)
/Solar+: J8.6, R2.2, Solar1.2, TP2.1
/Solar-: J8.5, Solar1.1
/TX0: J2.7, U1.31 (PD1(TXD/PCINT17))
Enable: U1.1 ((PCINT19/OC2B/INT1)PD3); also elsewhere on the board
GND: C1.1, C2.1, C3.1, C4.2, C5.2, C6.2, J1.1, J2.1, J3.1, J4.1, J5.1, J5.6, J7.1, J8.4, J15.1, J20.1, J20.2, J20.3, JP4.1 (A), JP5.1 (A), JP6.1 (A), R3.1, Reset1.3, TP5.1, U1.3 (GND), U1.5 (GND), U1.21 (GND), U8.6 (INH), U8.7 (VEE), U8.8 (VSS), U11.4 (V-), U12.10 (VSS), X1.2; also elsewhere on the board
unnamed: D30.2 (A), RV_LED1.1
unnamed: D30.1 (K), D31.1 (K), J15.2
unnamed: D31.2 (A), RV_LED2.1
unnamed: JP4.2 (B), R8.1, U12.15 (A0)
unnamed: JP5.2 (B), R7.1, U12.16 (A1)
unnamed: JP6.2 (B), R6.1, U12.17 (A2)
unnamed: U1.7 ((PCINT6/XTAL1/TOSC1)PB6), X1.1
unnamed: U1.8 ((PCINT7/XTAL2/TOSC2)PB7), X1.3
unnamed: C1.2, U1.20 (AREF)
unnamed: R2.1, R3.2, U11.3 (+)
unnamed: J4.12, U12.1 (GPB0)
unnamed: J4.11, U12.2 (GPB1)
unnamed: J4.10, U12.3 (GPB2)
unnamed: J4.9, U12.4 (GPB3)
unnamed: J4.8, U12.5 (GPB4)
unnamed: J4.7, U12.6 (GPB5)
unnamed: J4.6, U12.7 (GPB6)
unnamed: J4.5, U12.8 (GPB7)
Sens_Vent1: U1.23 (PC0(ADC0/PCINT8)); also elsewhere on the board
Sens_Vent2: U1.24 (PC1(ADC1/PCINT9)); also elsewhere on the board
Sens_Vent3: U1.25 (PC2(ADC2/PCINT10)); also elsewhere on the board
Sens_Vent4: U1.26 (PC3(ADC3/PCINT11)); also elsewhere on the board
Vent1_D1: U12.22 (GPA1); also elsewhere on the board
Vent1_D2: U12.21 (GPA0); also elsewhere on the board
Vent2_D1: U12.24 (GPA3); also elsewhere on the board
Vent2_D2: U12.23 (GPA2); also elsewhere on the board
Vent3_D1: U12.26 (GPA5); also elsewhere on the board
Vent3_D2: U12.25 (GPA4); also elsewhere on the board
Vent4_D1: U12.28 (GPA7); also elsewhere on the board
Vent4_D2: U12.27 (GPA6); also elsewhere on the board

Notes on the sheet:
Analog Pin Multiplexer
I/O Expander mit Ventilerweiterung
Bootloader/Code Upload
Atmega 328p-Au
Connections
LORA_E32
Gegenstück
Test Points
PWR 2Sec auf Low in setup um modul zu booten
USB_Volt
PINOUT SPANNUNGSVERSORGUNG SOLAR
DS3231 RTC
ANZEIGE LEDS
SIM7080G
OPVs Impedanzwandler
Reset Taster

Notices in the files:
hardware/01_Hauptplatine_V2/HauptplatineEIC_V2.kicad_pcb:
©️STECKTEC
